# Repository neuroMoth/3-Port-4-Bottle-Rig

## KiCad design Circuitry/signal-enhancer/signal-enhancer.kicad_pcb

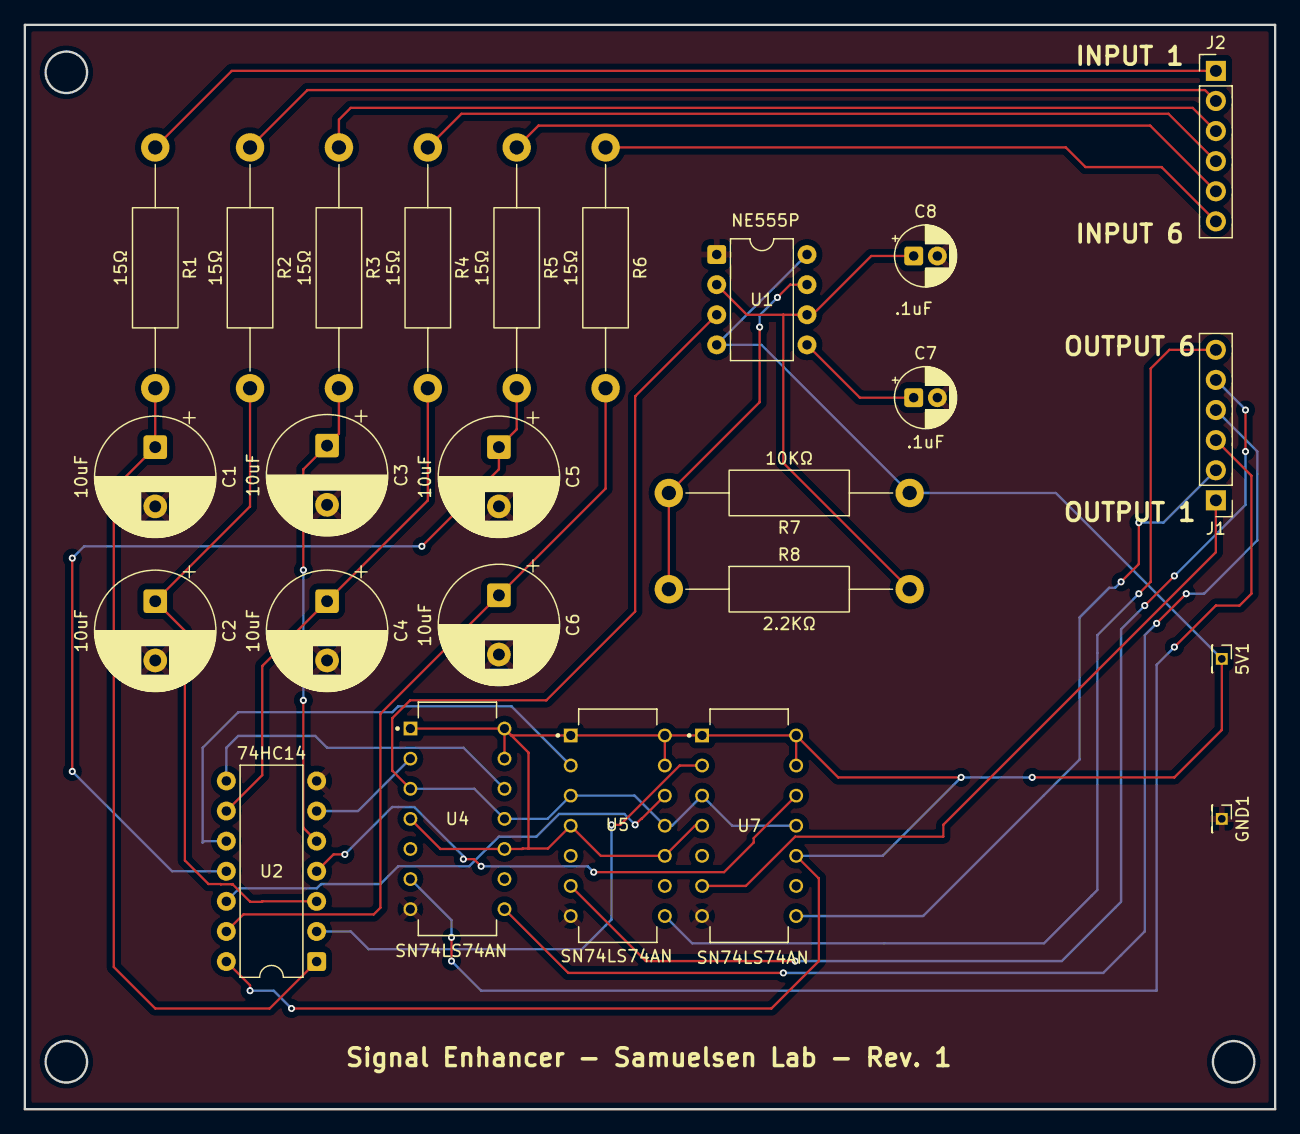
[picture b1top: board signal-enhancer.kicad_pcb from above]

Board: 2 copper layers, 105.5 x 91.5 mm, 25 parts (0 on the bottom side), 30 nets.

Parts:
5V1: Conn_01x01_Pin; PinHeader_1x01_P1.27mm_Vertical
C1, C2, C3, C4, C5, C6: 10uF; CP_Radial_D10.0mm_P5.00mm
C7, C8: .1uF; CP_Radial_D5.0mm_P2.00mm
GND1: Conn_01x01_Pin; PinHeader_1x01_P1.27mm_Vertical
J1, J2: Conn_01x06_Pin; PinHeader_1x06_P2.54mm_Vertical
R1, R2, R3, R4, R5, R6: 15Ω; R_Axial_DIN0411_L9.9mm_D3.6mm_P20.32mm_Horizontal
R7: 10KΩ; R_Axial_DIN0411_L9.9mm_D3.6mm_P20.32mm_Horizontal
R8: 2.2KΩ; R_Axial_DIN0411_L9.9mm_D3.6mm_P20.32mm_Horizontal
U1: NE555P; DIP-8_W7.62mm
U2: 74HC14; DIP-14_W7.62mm
U4, U5, U7: SN74LS74AN

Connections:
/5V: 5V1.1, R7.1, U1.4 (R), U1.8 (VCC), U2.14 (VCC), U4.1 (1~CLR), U4.4 (1~PRE), U4.10 (2~PRE), U4.13 (2~CLR), U4.14 (VCC), U5.1 (1~CLR), U5.4 (1~PRE), U5.10 (2~PRE), U5.13 (2~CLR), U5.14 (VCC), U7.1 (1~CLR), U7.4 (1~PRE), U7.10 (2~PRE), U7.13 (2~CLR), U7.14 (VCC)
/555_CLK: U1.3 (Q), U4.3 (1CLK), U4.11 (2CLK), U5.3 (1CLK), U5.11 (2CLK), U7.3 (1CLK), U7.11 (2CLK)
/GND: C1.2, C2.2, C3.2, C4.2, C5.2, C6.2, C7.2, C8.2, GND1.1, U1.1 (GND), U2.7 (GND), U4.7 (GND), U5.7 (GND), U7.7 (GND)
/IN_1: J2.1, R1.1
/IN_2: J2.2, R2.1
/IN_3: J2.3, R3.1
/IN_4: J2.4, R4.1
/IN_5: J2.5, R5.1
/IN_6: J2.6, R6.1
/OUT_1: J1.1, U7.6 (1~Q)
/OUT_2: J1.2, U7.8 (2~Q)
/OUT_3: J1.3, U4.6 (1~Q)
/OUT_4: J1.4, U4.8 (2~Q)
/OUT_5: J1.5, U5.6 (1~Q)
/OUT_6: J1.6, U5.8 (2~Q)
/SCHM_1: C1.1, R1.2, U2.1
/SCHM_2: C2.1, R2.2, U2.3
/SCHM_3: C3.1, R3.2, U2.5
/SCHM_4: C4.1, R4.2, U2.9
/SCHM_5: C5.1, R5.2, U2.11
/SCHM_6: C6.1, R6.2, U2.13
/pin_5: C7.1, U1.5 (CV)
/pin_6_to_2: C8.1, R8.2, U1.2 (TR), U1.6 (THR)
/r7_to_pin-7: R7.2, R8.1, U1.7 (DIS)
unnamed: U2.6, U4.2 (1D)
unnamed: U2.8, U4.12 (2D)
unnamed: U2.10, U5.2 (1D)
unnamed: U2.12, U5.12 (2D)
unnamed: U2.2, U7.2 (1D)
unnamed: U2.4, U7.12 (2D)

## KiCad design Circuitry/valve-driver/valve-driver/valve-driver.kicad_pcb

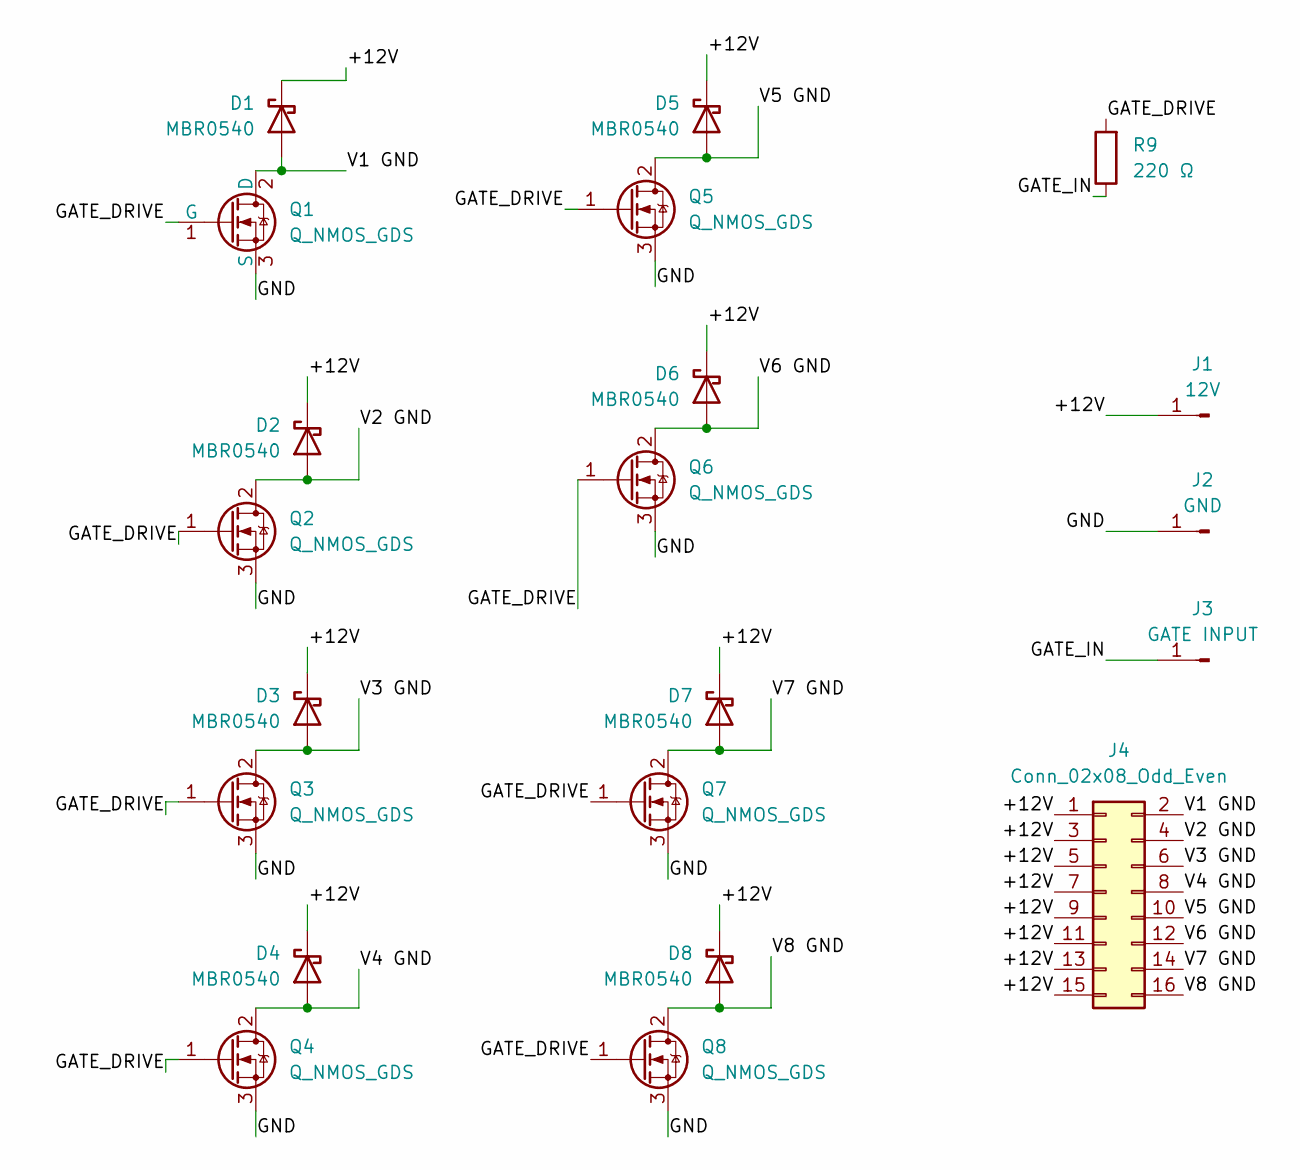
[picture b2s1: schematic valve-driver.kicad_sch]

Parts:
D1, D2, D3, D4, D5, D6, D7, D8: MBR0540; D_DO-15_P15.24mm_Horizontal
J1: 12V; PinHeader_1x01_P2.54mm_Vertical
J2: GND; PinHeader_1x01_P2.54mm_Vertical
J3: GATE INPUT; PinHeader_1x01_P2.54mm_Vertical
J4: Conn_02x08_Odd_Even; PinHeader_2x08_P2.54mm_Vertical
Q1, Q2, Q3, Q4, Q5, Q6, Q7, Q8: Q_NMOS_GDS; TO-220-3_Vertical
R9: 220 Ω; R_Axial_DIN0309_L9.0mm_D3.2mm_P15.24mm_Horizontal

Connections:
/+12V: D1.1 (K), D2.1 (K), D3.1 (K), D4.1 (K), D5.1 (K), D6.1 (K), D7.1 (K), D8.1 (K), J1.1, J4.1, J4.3, J4.5, J4.7, J4.9, J4.11, J4.13, J4.15
/GATE_DRIVE: Q1.1 (G), Q2.1 (G), Q3.1 (G), Q4.1 (G), Q5.1 (G), Q6.1 (G), Q7.1 (G), Q8.1 (G), R9.2
/GATE_IN: J3.1, R9.1
/GND: J2.1, Q1.3 (S), Q2.3 (S), Q3.3 (S), Q4.3 (S), Q5.3 (S), Q6.3 (S), Q7.3 (S), Q8.3 (S)
/V1 GND: D1.2 (A), J4.2, Q1.2 (D)
/V2 GND: D2.2 (A), J4.4, Q2.2 (D)
/V3 GND: D3.2 (A), J4.6, Q3.2 (D)
/V4 GND: D4.2 (A), J4.8, Q4.2 (D)
/V5 GND: D5.2 (A), J4.10, Q5.2 (D)
/V6 GND: D6.2 (A), J4.12, Q6.2 (D)
/V7 GND: D7.2 (A), J4.14, Q7.2 (D)
/V8 GND: D8.2 (A), J4.16, Q8.2 (D)

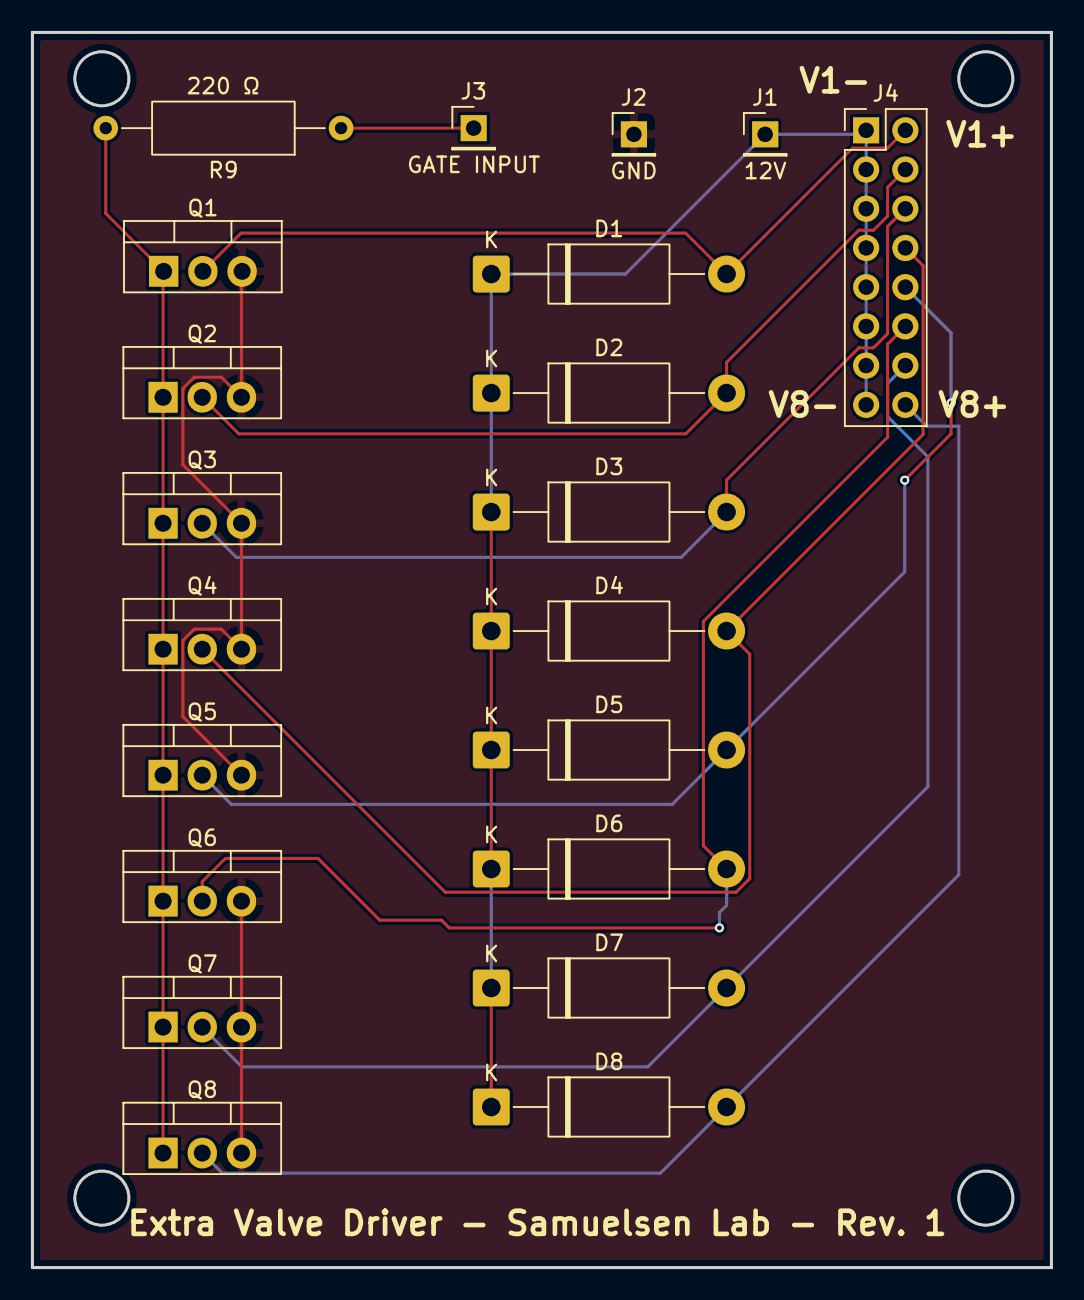
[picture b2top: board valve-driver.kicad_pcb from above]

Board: 2 copper layers, 66.0 x 80.0 mm, 21 parts (0 on the bottom side), 12 nets.

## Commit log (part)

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2025-05-14 first commit, faceplate for motion bracket
2025-05-19 c2d files for acryllic box
2025-05-22 spout door c2d
2025-07-11 add initial motor controlling code, printable gantry leg mount piece
2025-07-15 clean up and clarify, group motor information
2025-07-16 add Roberto's shared MATLAB scripts
2025-07-18 add updated Set_params script
2025-07-18 move default protocol, set_valve_open to external functions
2025-07-22 all movement commands functioning as expected
2025-07-24 Add cylinder holder CAD and STL files
    Added new SolidWorks part and assembly files for the cylinder holder, along with the corresponding printable STL file. Removed temporary and backup files to clean up the directory.
2025-07-28 Add signal enhancer files and update CAD models
    Added new KiCad project files, backups, and cache for the signal enhancer circuitry. Updated and added several CAD files for the cylinder holder and valve holder assemblies, and included new printabl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
2025-07-29 Update valve-driver and signal-enhancer PCB files
    Added new KiCad project files and backups for valve-driver. Updated signal-enhancer PCB and backup files. Modified several CAD and STL files for cylinder holder and valve-holder components.
2025-07-31 Add cage top and spout mount CAD/CNC files
    Added new CNC, DXF, STEP, SLDASM, SLDPRT, STL, and 3MF files for cage top with screws, cage assembly, spout mounts, and related components. Updated valve driver backup and modified cylinder holder as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
2025-08-05 solidworks updates & stls
    electronics box, screw based assembly for box, etc
2025-08-05 change center port structure
    change center port structure so that the back mounting piece and the front mounting piece are separated for easier printing
2025-08-07 clean up stl file structure, update solidworks files
    solidworks updates include the teflon mount bracket, and linear actuator bracket
2025-08-12 Add CNC and CAD files for pee tray and cylinder holder
    Added new .c2d files for pee tray extrusions and several temporary SolidWorks files for the cylinder holder assembly. Updated the cylinder holder STL file.
2025-08-12 Add pee tray alignment parts and update STL/3MF files
    Added new CAD and STL files for pee tray alignment parts and a 3MF assembly with alignment pieces. Removed temporary or backup SolidWorks files from the Cage and Pee Tray directories.
2025-08-18 ironed out bugs, provide basic template for all state machines
    - fixed bug keeping analogin1 active even after state machine finishes.
    - fixed bug that caused data not to be saved until the entire experiment
    was over.
    - provide odor right counterpart to side_training_day one
2025-08-21 finish alternation day one and prepare for random trials
    finished alternation and switched to 'correct' and 'incorrect' port
    selection model that is top down (center chosen first) rather than the
    other way around which made no sense. This will make the random script
    much easier to write.
2025-08-25 finish random day 1 and 2
    completed generation of the pseudorandom center port valve selection
    function and reduced ttc for both center and lateral ports. Next will
    clean up previous protocols with class based structure.
2025-08-25 Add new CAD and CNC files for rig assembly
    Added multiple new SolidWorks, DXF, C2D, STEP, and STL files for various rig assembly components, including vac splitter, pee tray, barrier strip covers, gantry post mounts, and hose adapters. Update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
2025-08-27 fix lateral 2s window bug.
2025-09-08 valve driver case
2025-09-08 Clean up file structure
    remove outdated files, consolidate duplicate folders and files, clean up file structure for clarity
2025-09-09 add misc c2d, new teflon spout ring
2025-09-13 The same edits as for alternation_6
2025-09-14 Edits to alternation_2, punish after tup for lateral ports and printing to command window
    Punish after time up for lateral, increase disengagement to 20, and some additional changes to make it easier to read progress in the command window.
2025-09-16 remove unused alternation files
2025-09-16 events is a reserved keyword, caused indentation issues
    fixed indentation issues with event keyword. also removed old test protcols that are no longer needed.
2025-09-16 update to markdown
2025-09-17 Random Training 1 Changes
    Punish after lateral TTC, printing to command line.
2025-09-18 add spout drain assembly parts
    built assembly to mount spouts in during draining procedure to reduce likelihood of valve damage.
2025-09-18 Adding side training day 7.
    Modified side training days 3-4. Now rewards the sixth center lick as well. 100 trials per session. 15 sec TTC.
2025-09-18 remove asv
2025-09-20 Rig-Assembly-Updates
2025-09-22 15s ITI, 0s Punish
    For alternation protocols 2, 4, and 6 nonconsecutive (left water odor right). Increase ITI to 15s, 0s punish, and change max trials to 160.
2025-09-23 random_training_1 timing edits
    15s ITI, 10s punish, reward 6th lick in the center port, and a couple minor output print changes.
2025-09-25 Added sessionSummary script to a new analysis folder
    Script I wrote to provide a quick summary of the previous session.
2025-09-27 Add testing protocol for water left, odor right
    Copy of random training 2. Exactly the same, just to keep training and testing data separate.
2025-09-30 Moving changes to the real testing protocol.
    Keeping old testing protocol as testingOLD. New testing protocol divides ITI into ITI_start, ITI_end, and ITI_punish. This allows for any extra licks after a correct lateral selection to be correctly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
2025-10-02 Test edit for random training 2 - consistent blank timings
    For testing with the rig. We want the blanks to have the same opening time for all valves.
2025-10-02 Adding random variance to blank timings for every opening.
    Make valves open within a range of +/- 10 ms for every valve opening to prevent any auditory cueing.
2025-10-03 Save blank open times to data. Report as skip when fewer than 6 licks.
    Report skip and punish for partial engagement.
2025-10-03 Remove old testing protocol
2025-10-08 Returning functionality for valves 3, 4, 6, and 7
    Now testing and random training 2 protocol scripts use all 8 valves to prevent rats learning to distinguish from the spout positions.
2025-10-11 View all channels on oscilloscope by default
    Edit to configure_analog_in for testing and random training 2.
2025-10-23 Adding new clamp for holding vac tubing to teflon on the spout.
    Edited version of the clamp for holding on to the spout on the delivery frame.
2025-12-05 Trying to vary number of dry licks - modifying global counter per trial
    Just a test.
2025-12-06 Attempt at having a single valve opening, plus edit to protocol settings
    Editing states in the experimental protocol to have a single valve opening for center and correct lateral instead of 3x each per trial. Also edited some values to see if they allow selecting 30ul of 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
    Also, some adjustments to blank valve jitter.
2025-12-08 Updating and cleaning up set_param protocol
    Commenting out parts we don't use, and adjusting the range of target liquid amounts.
2025-12-10 Moving around old files, renaming current set_parameters protocol, improvements and adjustments to single valve open protocol.
    Made some fixes to the timing and jitter. Reorganized so that some old files are no longer in the way. Renamed the current Set_exp_parameters protocol to separate from RV's version.
2025-12-12 Adding a couple of the new 3d printed parts
    Spout vac connector and tubing clamps.
2025-12-13 Update singleValveOpening protocol parameter location and session end conditions
2026-01-09 edits in progress - moving computer
2026-01-13 Additional adjustments to valve order randomization. Adjusted softcode for reporting engaged trials.
    Now valves can't repeat more than twice even if the same side repeats more, as long as there are enough valves. Engagement reporting should be more accurate.
2026-01-13 Adjusted timing of stimulus window. Commented out disengagement code.
2026-01-14 Adjusted reward licks and alternation progress.
2026-01-15 Revert "Adjusted reward licks and alternation progress."
    This reverts commit a18a60c1374740aca8c8169e670e1b061956877f.
2026-01-15 A few adjustments to get alternation to work.
    Made a couple silly mistakes which were easy to fix. Also fixed some reporting issues for engagement. NOTE: adjust how lateral dry licks are treated when incorrect. Right now seems to be short.
2026-01-15 Small fix to add final incorrect lick.
2026-01-15 Adding additional alteration training days for water left odor right v2.
    8 nonconsecutive repeats, 6, 4, and 2.
2026-01-19 Prototype for v2 side training protocol.
    This version is designed to incorporate subject-dependent session parameters.
2026-01-19 Edits to side training 1 and 2.
2026-01-20 Reorganizing protocols
2026-01-22 Test of testing protocol for water right, odor left
    Changes made to expVariables and PortHandler to manage the correct and incorrect conditions.
2026-01-22 Updated testing protocol for water left odor right to match updates
2026-01-26 Updated set_exp_parameters protocol to allow for different stimulus amounts for center vs lateral
2026-01-28 Update default settings selection
2026-02-14 Adding STLs for updated syringe/valve holder components
    Also some reorganizing in rig assembly STLs. Version 3 = components I (TVD) heavily modified or made for the current frame (for sound dampening).
2026-02-16 Revert "Prototype general testing 2OC task protocol using subject data to determine correct condition"
    This reverts commit 65c28494c1033f4e30bb4e9929bbb9810c4f4b7d.
2026-02-18 Add display subject name to testing_v2 and set params
2026-02-23 Updated Random Training 1 and 2 based on testing v2
2026-02-23 Updated lick familiarization and alternation protocols for v2
2026-02-24 Update session summary to calculate estimate consumed with 40ul per correct
2026-02-24 Updating PortHandler to receive the door for each port. Plus the rest of the v2 alternation protocols.
2026-02-24 Updated cage leg STL files
2026-02-25 Dumb mistake
2026-02-25 Fix attempt for side training 1 with 1 dry lick
    Global counters can't do 1 instance. Adjusted state structure instead.
2026-02-26 Add: valve priming and dry lick skip after 5 second break from licking for day02 familiarization
2026-03-01 Updating some print and stl files for cage components and pressure cap
2026-03-02 Adding to general functions for protocols. More reorganizing and updating of print and stl files.
2026-03-04 Stop experiment and update valve times are now general functions
2026-03-04 Adding experiment timer update to the rest of the side training protocols. Adding 8s ITI for last two days of side training.
2026-03-08 Adding fixed experiment timer to all protocols (except lick familiarization)
    Now we have an experiment timer that works. I can remove the nonfunctional one later.
2026-03-09 All Doors Down opens settings window to control valves
2026-03-13 Random training protocols have a max time of 1 hour. Only testing can go over.
2026-03-16 More adjustments to printing cage legs and door alignment parts
2026-03-20 Adding to max time for random 2 and testing. Also add time and message to alldoorsdown.
2026-03-28 More organizing and adding updated stls
2026-04-06 Updating syringe holder top and spout clamp and bracket files
2026-05-26 Revert "Valves can't repeat (doesn't affect side trial order)"
    This reverts commit d0c6b502fe54d0badd8db7792d43a4c47857dda8.
2026-05-27 Adding c2d files for faceplates and doors
    It looks like some of these were lost from a previous commit on Blake's version?
2026-05-31 First attempt at test protocol w lick offset events
    Also: minor update to pivot mount design for animal box latches
2026-06-03 2nd lick offset test protocol (pulsed stimulus delivery)
    Intended to be used with 10ul per lick for 3 licks during sampling and 4 licks for reward.
